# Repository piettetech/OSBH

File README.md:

#Open Source Beehives Project #
#Alpha Sensor Kit 0.4 #
====================================================

Developed for Open Source Beehives Project
http://opensourcebeehives.net

Some files are Copyright 2014 Scott Piette (scott.piette@gmail.com) <br>
Main example is Copyright 2014 Open Source Beehives Project (www.opensourcebeehives.net)

**Spark Core Alpha 0.4 Version**

The Alpha sensor kit is able to measure:

* Temperature
* Humidity
* Weight
* Audio frequency

It uses 2x DHT22 Temperature and Humidity sensors and 2x DS18B20 Temperature Sensors. 

The application is built upon a unified sensor framework that allows for adding different sensors in the future.
NOTE: v0.4 implements the weight and audio sensors without the unified sensor framework -> will be done in the future.

**List of equipment in the Alpha Version**

* (1) DHT22 sensor is used for monitoring outdoor Temperature and Humidity
* (1) DHT22 sensor is used for monitoring hive Temperature and Humidity
* (2) DS18B20 sensors are for monitoring Temperatures in other locations inside the beehive.
* (1) H30A Load Cell is used for measuring weight of the hive
* (1) Microphone is used to record bees inside the hive 
* (1) microSD CARD to store data

Data is collected every ten minutes and reported to a internet server running the SparkFun Phant database.
In Parallel Data can be saved offline to the SD Card.

**Installation**
------------
install spark-client software and compile the files included in spark.include via

spark compile firmware OSBH.bin

flash the spark via internet or usb connection

sudo spark flash --usb OSBH.bin

**Hardware**
--------

***solder the alpha PCB board***

find the eagle schematics under hardware

**License**
--------
This application contains several libraries and files.  Check the comments section of the .cpp and .h files for the specific details on the licenses.

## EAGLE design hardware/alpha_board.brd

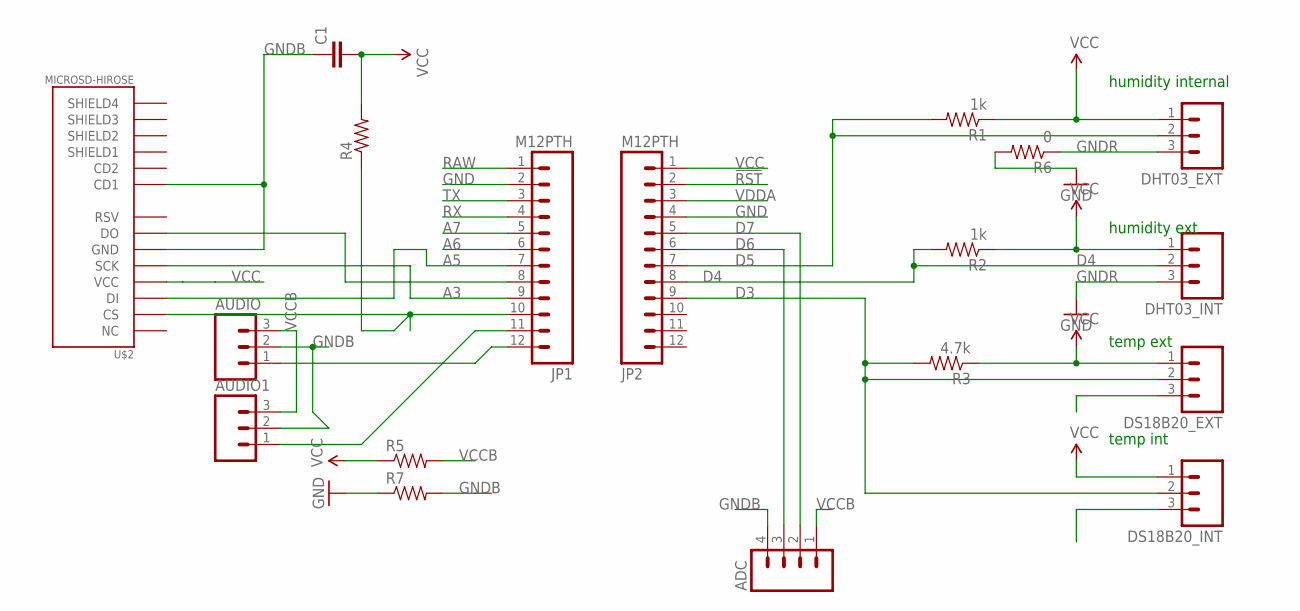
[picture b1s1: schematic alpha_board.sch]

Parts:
ADC: M04LOCK_LONGPADS; 1X04_LOCK_LONGPADS
AUDIO, AUDIO1: M03LOCK; 1X03_LOCK
C1: CAP1206; 1206
DHT03_EXT, DHT03_INT: M03LOCK; 1X03_LOCK
DS18B20_EXT, DS18B20_INT: M03LOCK; 1X03_LOCK
JP1, JP2: M12PTH; 1X12-SMALL-PADS
R1, R2: 1k; 1206
R3: 4.7k; 1206
R4, R5, R7: RESISTOR1206; 1206
R6: 0; 1206
U$2: MICROSD-HIROSE; MICROSD_HOLDER-HIROSE-DM3AT

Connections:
!RST: JP2.2
A3: JP1.9, U$2.CLK (SCK)
A5: JP1.7, U$2.CMD (DI)
A6: JP1.6
A7: JP1.5
D3: DS18B20_EXT.2, DS18B20_INT.2, JP2.9, R3.2
D4: DHT03_INT.2, JP2.8, R2.2
D5: DHT03_EXT.2, JP2.7, R1.2
D6: ADC.3, JP2.6
D7: ADC.2, JP2.5
GND: JP1.2, JP2.4, R6.2, R7.1
GNDB: ADC.4, AUDIO.2, AUDIO1.2, C1.1, DS18B20_EXT.3, DS18B20_INT.3, R7.2, U$2.CD1, U$2.VSS (GND)
GNDR: DHT03_EXT.3, DHT03_INT.3, R6.1
unnamed: JP1.10, R4.1, U$2.DAT3 (CS)
unnamed: AUDIO.1, JP1.12
unnamed: JP1.8, U$2.DAT0 (DO)
unnamed: AUDIO1.1, JP1.11
RAW: JP1.1
RX: JP1.4
TX: JP1.3
VCC: C1.2, DHT03_EXT.1, DHT03_INT.1, DS18B20_EXT.1, DS18B20_INT.1, JP2.1, R1.1, R2.1, R3.1, R4.2, R5.1, U$2.VDD (VCC)
VCCB: ADC.1, AUDIO.3, AUDIO1.3, R5.2
VDDA: JP2.3

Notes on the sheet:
humidity internal
temp int
temp ext
humidity ext

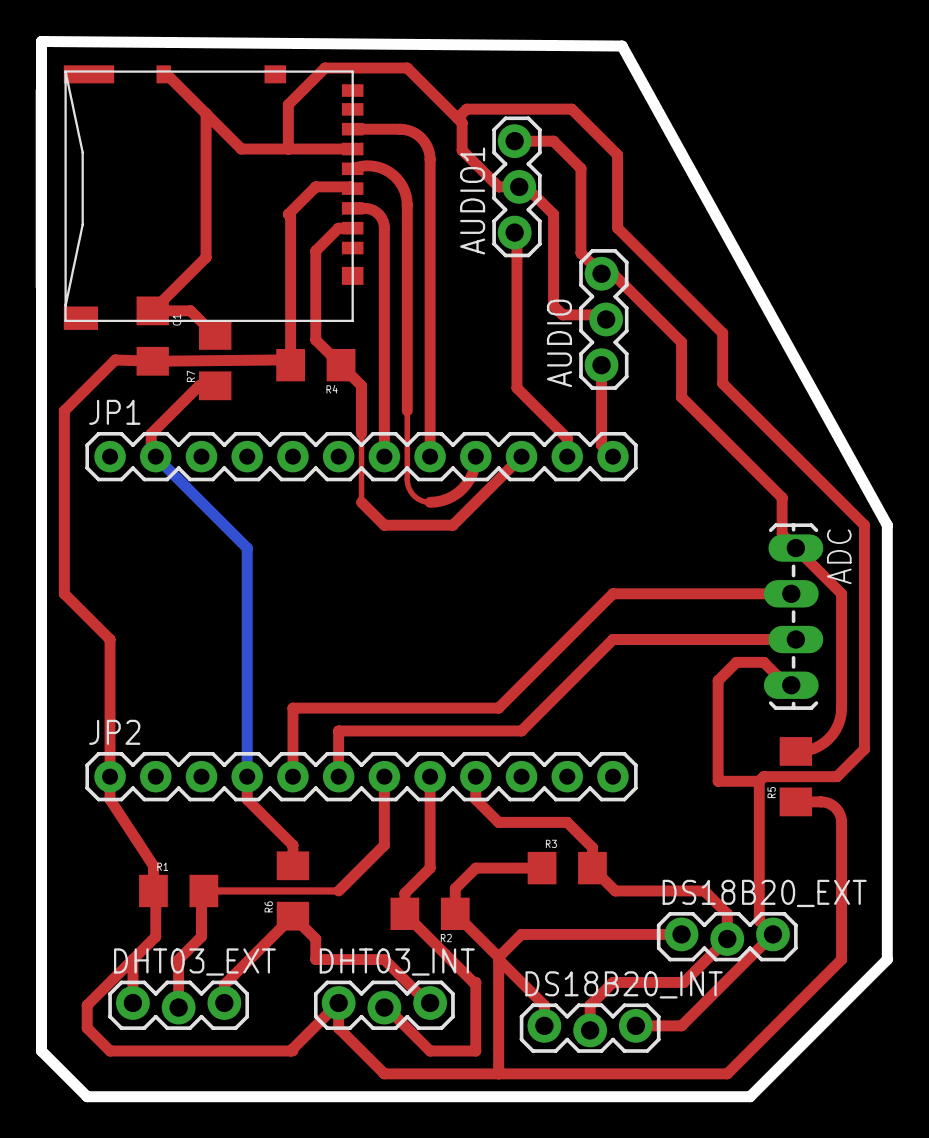
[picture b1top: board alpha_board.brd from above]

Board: 2 copper layers, 47.0 x 58.6 mm, 18 parts (0 on the bottom side), 16 nets.

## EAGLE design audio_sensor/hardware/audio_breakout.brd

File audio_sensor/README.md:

#Open Source Beehives Project #
#Audio Sensor 0.1 #
====================================================

Developed by Open Source Beehives Project
http://opensourcebeehives.net

Copyright 2014 Open Source Beehives Project (www.opensourcebeehives.net)

** Audio Sensor Version 0.1 **
--------
This Sensor is taking audio samples at a defined sampling rate and performing a Fast-Fourier-Transformation.

The hardware is basicly an amplifying circuit with low pass filter features connected to analog pin 1 of the spark core.
Example found on https://courses.cit.cornell.edu/bionb440/datasheets/SingleSupply.pdf

The used circuit is an adaption of the sparkfun board breakout: https://courses.cit.cornell.edu/bionb440/datasheets/SingleSupply.pdf and uses an 
100pF capacitor instead of 12pf and a 22uF input decoupling capacitor instead of an 1uF.

The Code is based on the kissFFT library by benswift. Read the code comments for more information.

**Test output of the FFT Code**

**License**
--------

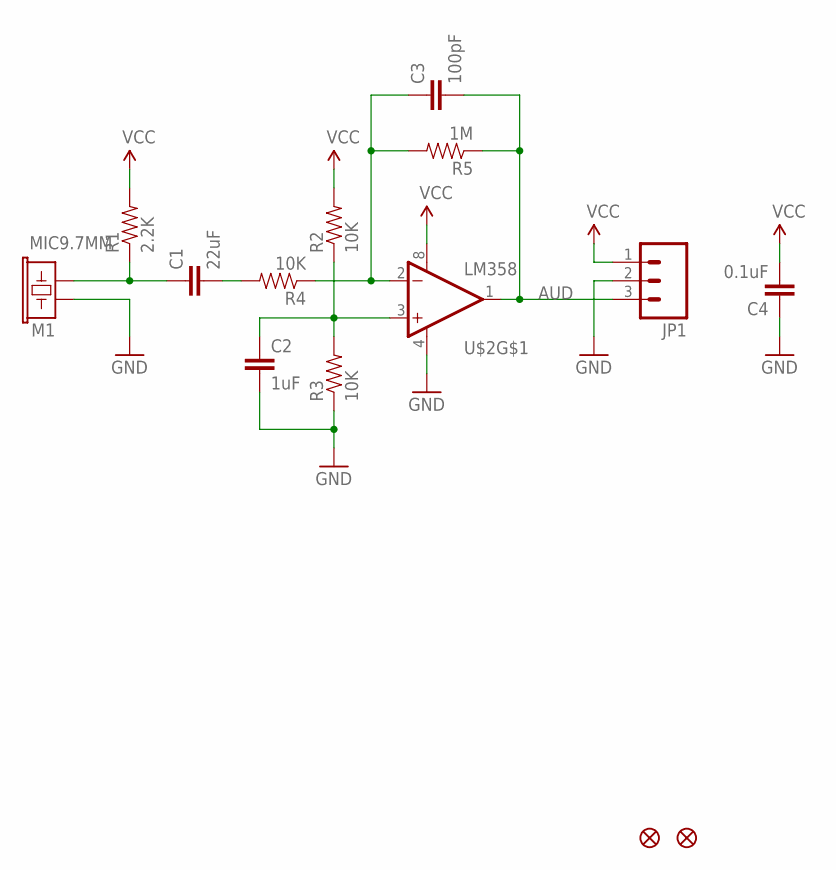
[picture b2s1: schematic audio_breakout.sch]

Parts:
C1: 22uF; 1206
C2: 1uF; 1206
C3: 100pF; 1206
C4: 0.1uF; 1206
JP1: M03PTH; 1X03
JP2, JP3: FIDUCIAL1X2; FIDUCIAL-1X2
M1: MIC9.7MM; MIC-9.7MM
R1: 2.2K; 1206
R2, R3, R4: 10K; 1206
R5: 1M; 1206
U$2: LM358; DIP08

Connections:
AUD: C3.2, JP1.3, R5.1, U$2.1 (OUT)
GND: C2.2, C4.1, JP1.2, M1.2, R3.1, U$2.4 (V-)
unnamed: C1.1, M1.1, R1.1
unnamed: C3.1, R4.1, R5.2, U$2.2 (-IN)
unnamed: C1.2, R4.2
unnamed: C2.1, R2.1, R3.2, U$2.3 (+IN)
VCC: C4.2, JP1.1, R1.2, R2.2, U$2.8 (V+)

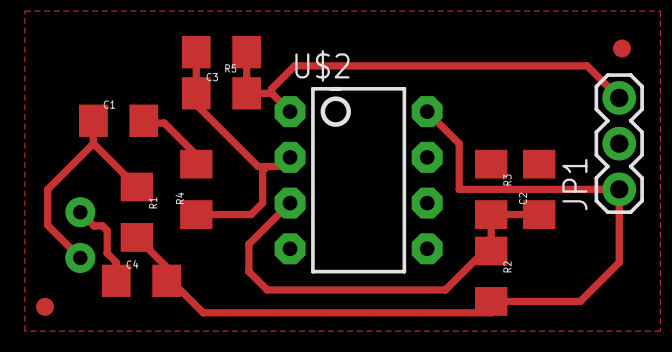
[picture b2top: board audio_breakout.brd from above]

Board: 2 copper layers, 14 parts (1 on the bottom side), 7 nets.

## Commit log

2014-10-16 OSBH Version a1.0
    Initial commit of alpha version 1.0
2014-10-23 Updated for Spark Library IDE
    Updated for the Spark Library
2014-10-23 Updating Readme.md to use Spark IDE
    Updated Readme to reflect using the Spark IDE as a library
2014-10-23 Added OSBH.h
2014-10-23 Added libraries
    PietteTech_DHT
    PietteTech_Phant
2014-10-23 Renamed OSBH_App to App_OSBH
    Renamed example to appear first in list on Spark IDE
2014-10-23 Update headers
    Updated comments for consistency
2014-11-13 Initial v0.2 Alpha commit
    Alpha v0.2 release of Open Source Beehives Project Sensor Kit based on
    Spark Core
2014-11-13 Updated readme
    Updated read
2014-11-13 Updated README.md
    Updated README.md
2014-11-13 Updated README.md file
    Updated README.md file
2014-11-13 Fixed release version
    fixed release version
2015-01-16 adding alpha PCB Design
2015-01-16 Readme.md: adding pcb hardware
2015-01-17 README.md update
2015-01-22 audio sensor alpha version upload
2015-02-03 frequency analysis added

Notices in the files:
parts and their libraries:
SparkFun: Licensing: CC v3.0 Share-Alike You are welcome to use this library for commercial purposes.
SparkFun-Connectors: Licensing: Creative Commons ShareAlike 4.0 International - https://creativecommons.org/licenses/by-sa/4.0
